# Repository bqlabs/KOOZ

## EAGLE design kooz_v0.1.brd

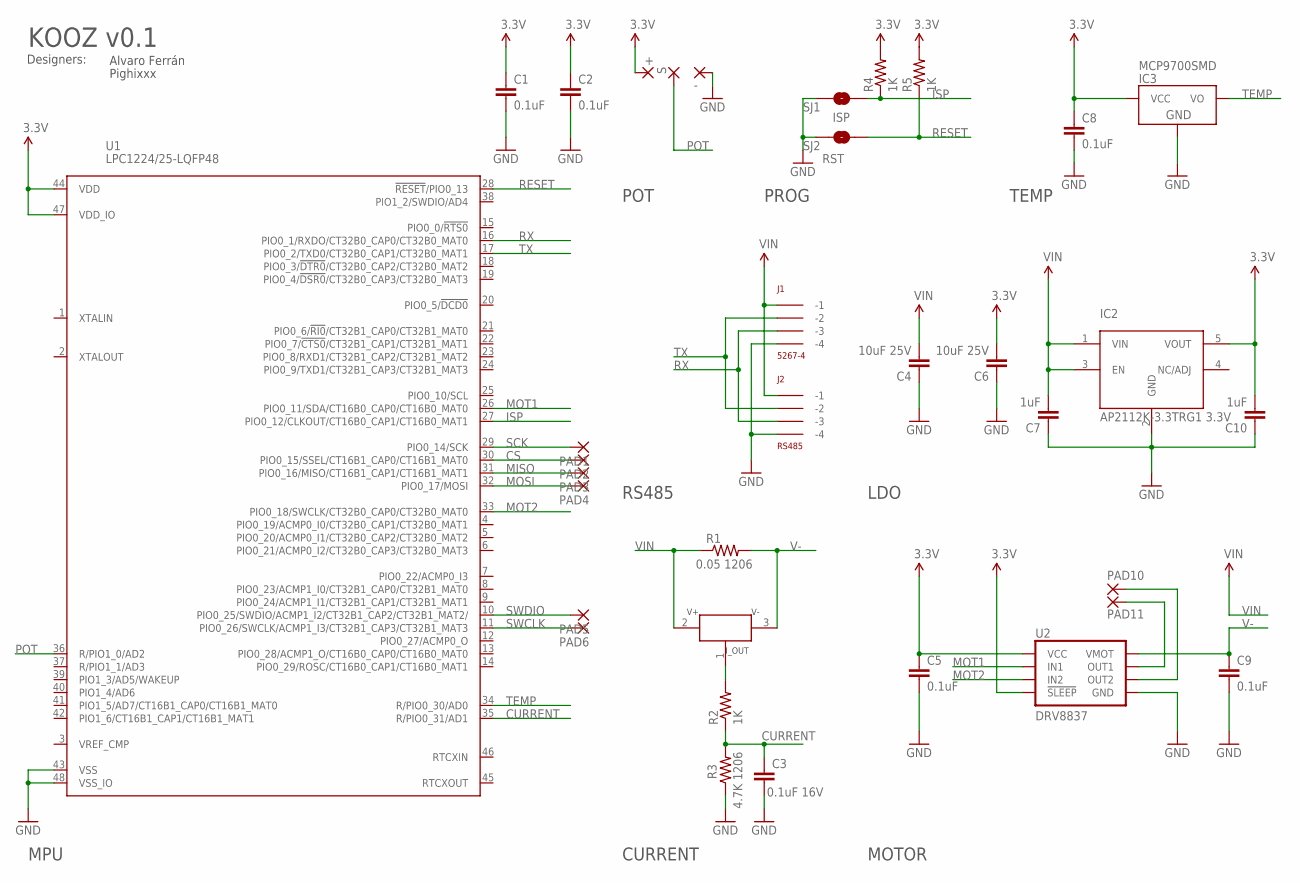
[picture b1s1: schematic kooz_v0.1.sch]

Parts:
C1, C2, C5, C8, C9: 0.1uF; 0402-CAP
C3: 0.1uF 16V; 0402-CAP
C4, C6: 10uF 25V; 0603-CAP
C7, C10: 1uF; 0402-CAP
IC1: ZXCT1008; SOT23
IC2: AP2112K-3.3TRG1 3.3V; SOT23-5
IC3: MCP9700SMD; SOT23-3
J1: 5267-4
J2: RS485; 5267-4
PAD1, PAD2, PAD3, PAD4, PAD5, PAD6: SMD2; SMD1,27-2,54
PAD7: +; 2,54/1,1
PAD8: S; 2,54/1,1
PAD9: -; 2,54/1,1
PAD10, PAD11: 2,54/1,1
R1: 0.05 1206; 1206-RES
R2, R4, R5: 1K; 0402-RES
R3: 4.7K 1206; 1206-RES
SJ1: ISP; SJ_2S-NO
SJ2: RST; SJ_2S-NO
U1: LPC1224/25-LQFP48; LQFP48
U2: DRV8837; DSG

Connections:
3.3V: C1.1, C2.1, C5.1, C6.2, C8.1, C10.2, IC2.5 (VOUT), IC3.1 (VCC), PAD7.1, R4.2, R5.2, U1.44 (VDD), U1.47 (VDD_IO), U2.7 (!SLEEP), U2.8 (VCC)
CS: PAD2.1, U1.30 (PIO0_15/SSEL/CT16B1_CAP0/CT16B1_MAT0)
CURRENT: C3.1, R2.1, R3.2, U1.35 (R/PIO0_31/AD1)
GND: C1.2, C2.2, C3.2, C4.1, C5.2, C6.1, C7.1, C8.2, C9.2, C10.1, IC2.2 (GND), IC3.3 (GND), J1.P$4 (-4), J2.P$4 (-4), PAD9.1, R3.1, SJ1.1, SJ2.1, U1.43 (VSS), U1.48 (VSS_IO), U2.4 (GND), U2.PAD (GND)
ISP: R4.1, SJ1.2, U1.27 (PIO0_12/CLKOUT/CT16B0_CAP1/CT16B0_MAT1)
MISO: PAD3.1, U1.31 (PIO0_16/MISO/CT16B1_CAP1/CT16B1_MAT1)
MOSI: PAD4.1, U1.32 (PIO0_17/MOSI)
MOT1: U1.26 (PIO0_11/SDA/CT16B0_CAP0/CT16B0_MAT0), U2.6 (IN1)
MOT2: U1.33 (PIO0_18/SWCLK/CT32B0_CAP0/CT32B0_MAT0), U2.5 (IN2)
unnamed: PAD11.1, U2.2 (OUT1)
unnamed: PAD10.1, U2.3 (OUT2)
unnamed: IC1.1 (I_OUT), R2.2
POT: PAD8.1, U1.36 (R/PIO1_0/AD2)
RESET: R5.1, SJ2.2, U1.28 (!RESET!/PIO0_13)
RX: J1.P$3 (-3), J2.P$3 (-3), U1.16 (PIO0_1/RXDO/CT32B0_CAP0/CT32B0_MAT0)
SCK: PAD1.1, U1.29 (PIO0_14/SCK)
SWCLK: PAD6.1, U1.11 (PIO0_26/SWCLK/ACMP1_I3/CT32B1_CAP3/CT32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)
SWDIO: PAD5.1, U1.10 (PIO0_25/SWDIO/ACMP1_I2/CT32B1_CAP2/CT32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)
TEMP: IC3.2 (VO), U1.34 (R/PIO0_30/AD0)
TX: J1.P$2 (-2), J2.P$2 (-2), U1.17 (PIO0_2/TXD0/CT32B0_CAP1/CT32B0_MAT1)
V-: C9.1, IC1.3 (V-), R1.2, U2.1 (VMOT)
VIN: C4.2, C7.2, IC1.2 (V+), IC2.1 (VIN), IC2.3 (EN), J1.P$1 (-1), J2.P$1 (-1), R1.1

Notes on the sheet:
KOOZ v0.1
Designers:
Alvaro Ferrán
Pighixxx
POT
TEMP
RS485
LDO
MOTOR
CURRENT
MPU
PROG

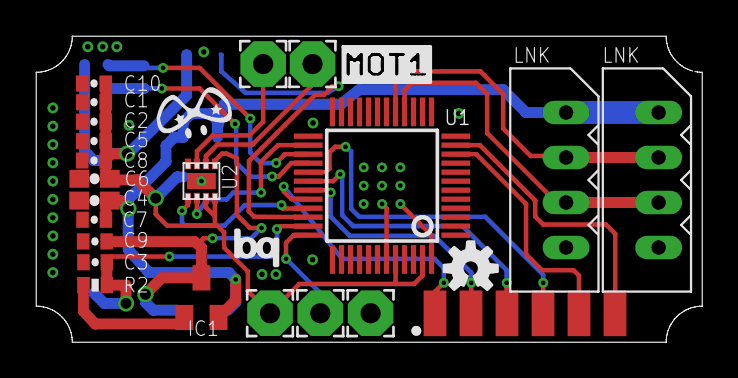
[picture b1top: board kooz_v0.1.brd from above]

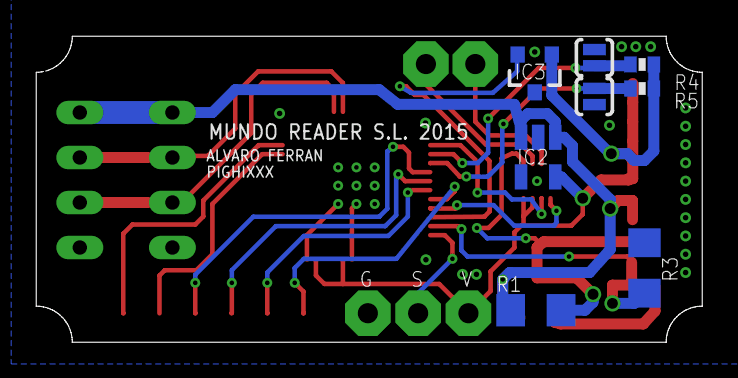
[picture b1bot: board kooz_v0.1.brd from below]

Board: 2 copper layers, 37.0 x 17.0 mm, 39 parts (8 on the bottom side), 22 nets.

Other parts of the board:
LOGO1: OSHW-LOGOS; OSHW-LOGO-S
U$1: S_MOT1
U$2: PIGHIXXX_LOGO
U$3: BQ_LOGO_SMALL

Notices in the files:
parts and their libraries:
SparkFun-Sensors: Licensing: Creative Commons ShareAlike 4.0 International - https://creativecommons.org/licenses/by-sa/4.0
